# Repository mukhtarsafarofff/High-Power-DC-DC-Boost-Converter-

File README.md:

(ENG)  A boost converter is a DC-DC type switching converter that steps up the voltage while maintaining a constant power balance. This  high-efficiency boost converter circuit based on the popular TL494 IC, which has a minimum supply voltage of 7V and a maximum of 40V.Here i have used IF540N Mosfet as Switch.When the MOSFET is on, the inductor starts charging, the current through the inductor keeps on increasing, which gets stored in the form of a magnetic field.When the  MOSFET turns off, the magnetic field starts to collapse, and the current flows in the direction opposite of the charging current and it starts charging the capacitor.By continuously making the switch (MOSFET) on and off, I have created an output voltage that is greater than the input voltage. Now, i can control the output voltage by controlling the on and the off-time of the switch, and that is what we are doing in the main circuit. The 5V internal reference regulator output of TL494 IC's is the REF pin, which is pin-14 of the IC. The reference regulator is there to provide a stable supply for internal circuitry like the pulse-steering flip-flop, oscillator, dead-time control comparator, and PWM comparator.The frequency of the oscillator can be set by selecting timing components RT and CT. The regulator is also used to drive the error amplifiers which are responsible for controlling the output.The oscillator generates and provides a sawtooth wave to the dead time controller and the PWM comparators for various control signals and the oscillator frequency is equal to the output frequency only for single-ended applications. For push-pull applications, the output frequency is one-half of the oscillator frequency.This IC has two internal output transistors which are in open-collector and open-emitter configurations, by which it can source or sink a maximum current up to 200mA.This circuit can handle a maximum current of 19Amps,so when we want more Amps we need to change our inductor to biggest one .This TL494 Boost Converter circuit is made up of components that are very easily obtainable and this circuit can easily handle power more than 100Watts.If we are connecting a big load to the output of this boost converter circuit, a huge amount of current will flow through the PCB traces, and there's a chance that the traces will burn out. So, to prevent the PCB traces from burning out, we have increased the trace thickness as much as possible. Also, we have reinforced the PCB traces with a thick layer of solder to lower the trace resistance.When we want to  construct this circuit in handmade PCB , we must  reinforce the PCB traces with a thick layer of solder to lower the trace resistance and we need to attach a heatsink to the mosfet.To test the circuit I have used 12V power supply as input.I have attached a voltmeter and an ammeter to the output of the circuit which shows the output voltage and output current. From which we can easily calculate the output power for this circuit. 

(DEU)   Ein Aufwärtswandler ist ein Gleichstrom-Gleichstrom-Schaltwandler, der die Spannung erhöht und gleichzeitig ein konstantes Leistungsgleichgewicht aufrechterhält. Diese hocheffiziente Aufwärtswandlerschaltung basiert auf dem beliebten TL494-IC, der eine minimale Versorgungsspannung von 7 V und eine maximale Versorgungsspannung von 40 V hat. Da wir den IRF540N MOSFET als Schalter verwenden.Während der MOSFET eingeschaltet bleibt, beginnt die Spule sich aufzuladen, der Strom durch die Spule steigt ständig an, was in Form eines Magnetfeldes gespeichert wird.Wenn der MOSFET sich ausschaltet, beginnt das Magnetfeld zusammenzubrechen, und der Strom fließt in die entgegengesetzte Richtung des Ladevorgangsstroms und dies beginnt den Kondesator aufzuladen.Indem ich den Schalter (MOSFET) kontinuierlich ein- und ausschalten, habe ich  eine Ausgangsspannung erzeugt, die größer ist als die Eingangsspannung.Jetzt kann ich die Ausgangsspannung kontrollieren, indem ich die Ein- und Ausschaltzeit des Schalters steuere, und das ist es, was wir im Hauptkreis tun.Die Ausgabe des internen Referenzreglers mit 5V des TL494 ICs ist der REF-Pin, der Pin 14 des ICs. Der Referenzregler dient dazu, eine stabile Versorgung für die interne Schaltung wie den Pulslenk-Flip-Flop, den Oszillator, den Totzeitregelkomparator und den PWM-Komparator bereitzustellen.Die Frequenz des Oszillators kann durch Auswahl der Zeitkomponenten RT und CT eingestellt werden.Der Regler wird auch verwendet, um die Fehlerverstärker anzutreiben, die für die Steuerung des Ausgangs verantwortlich sind.Der Oszillator erzeugt und liefert eine Sägezahnwelle an den Totzeitregler und die PWM-Komparatoren für verschiedene Steuersignale, und die Oszillatorfrequenz entspricht nur für einseitige Anwendungen der Ausgangsfrequenz.Für Gegentaktschaltungen beträgt die Ausgangsfrequenz die Hälfte der Oszillatorfrequenz.Der IC verfügt über zwei interne Ausgangstransistoren, die in Open-Collector- und Open-Emitter-Konfigurationen sind, wodurch er maximal einen Strom von bis zu 200 mA liefern oder aufnehmen kann.Diese Schaltung kann einen maximalen Strom von 19 Ampere handhaben. Wenn wir eine große Last an den Ausgang dieses Boost-Konverter-Schaltkreises anschließen, wird eine enorme Menge an Strom durch die Leiterbahnen der Leiterplatte fließen, und es besteht die Gefahr, dass die Leiterbahnen durchbrennen.Um das Durchbrennen der Leiterbahnen zu verhindern, haben wir die Leiterbahndicke so weit wie möglich erhöht. Außerdem haben wir die Leiterbahnen der Leiterplatte mit einer dicken Schicht Lötzinn verstärkt, um den Leiterbahnwiderstand zu verringern.Wenn wir diesen Schaltkreis auf einer handgefertigten Leiterplatte herstellen möchten, müssen wir die Leiterbahnen der Leiterplatte mit einer dicken Schicht Lötzinn verstärken, um den Leiterbahnwiderstand zu verringern, und wir müssen einen Kühlkörper an den MOSFET anbringen. Wenn wir diesen Schaltkreis auf einer handgefertigten Leiterplatte herstellen möchten, müssen wir die Leiterbahnen der Leiterplatte mit einer dicken Schicht Lötzinn verstärken, um den Leiterbahnwiderstand zu verringern, und wir müssen einen Kühlkörper an den MOSFET anbringen. Um den Schaltkreis zu testen, habe ich eine 12-Volt-Stromversorgung als Eingang verwendet.Ich habe ein Voltmeter und ein Amperemeter an den Ausgang des Schaltkreises angeschlossen, die die Ausgangsspannung und den Ausgangsstrom anzeigen. Dadurch können wir die Ausgangsleistung für diesen Schaltkreis leicht berechnen.

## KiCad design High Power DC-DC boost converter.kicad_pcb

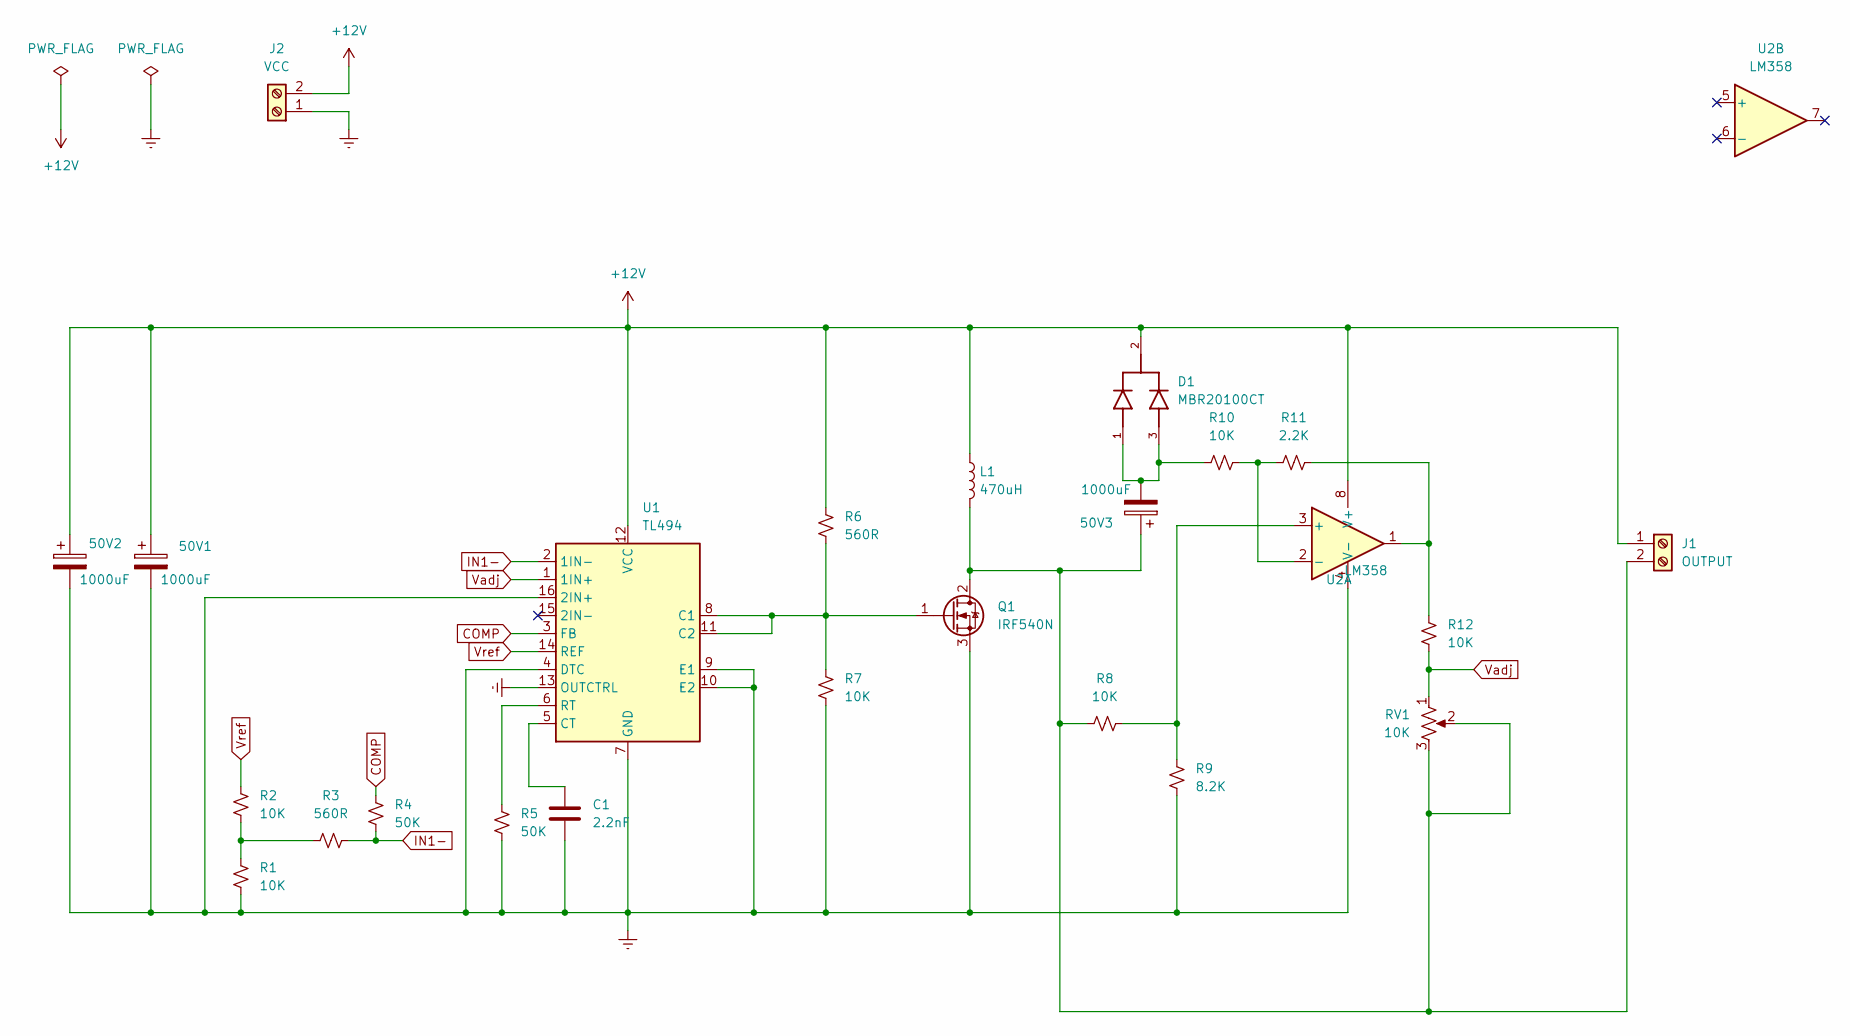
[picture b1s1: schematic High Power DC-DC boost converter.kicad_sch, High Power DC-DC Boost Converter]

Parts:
50V1, 50V2, 50V3: 1000uF; CP_Radial_D13.0mm_P7.50mm
C1: 2.2nF; C_Disc_D7.5mm_W5.0mm_P7.50mm
D1: MBR20100CT; TO254P1066X482X2286-3; PARTREV 8-2
J1: OUTPUT; TerminalBlock_bornier-2_P5.08mm
J2: VCC; TerminalBlock_bornier-2_P5.08mm
L1: 470uH; L_Toroid_Vertical_L24.6mm_W15.5mm_P11.44mm_Pulse_KM-4
Q1: IRF540N; TO-220-3_Vertical
R1, R2, R7, R8, R10, R12: 10K; R_Axial_DIN0411_L9.9mm_D3.6mm_P15.24mm_Horizontal
R3, R6: 560R; R_Axial_DIN0411_L9.9mm_D3.6mm_P15.24mm_Horizontal
R4, R5: 50K; R_Axial_DIN0411_L9.9mm_D3.6mm_P15.24mm_Horizontal
R9: 8.2K; R_Axial_DIN0411_L9.9mm_D3.6mm_P15.24mm_Horizontal
R11: 2.2K; R_Axial_DIN0411_L9.9mm_D3.6mm_P15.24mm_Horizontal
RV1: 10K; Potentiometer_Vishay_148-149_Single_Horizontal
U1: TL494; DIP-16_W7.62mm
U2: LM358; DIP-8_W7.62mm

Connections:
+12V: 50V1.1, 50V2.1, D1.2, J1.1, J2.2, L1.1, R6.2, U1.12 (VCC), U2.8 (V+)
COMP: R4.2, U1.3 (FB)
Earth: 50V1.2, 50V2.2, C1.2, J2.1, Q1.3 (S), R1.2, R5.1, R7.1, R9.2, U1.4 (DTC), U1.7 (GND), U1.9 (E1), U1.10 (E2), U1.13 (OUTCTRL), U1.16 (2IN+), U2.4 (V-)
IN1-: R3.2, R4.1, U1.2 (1IN-)
unnamed: 50V3.2, D1.1, D1.3, R10.2
unnamed: 50V3.1, J1.2, L1.2, Q1.2 (D), R8.2, RV1.2, RV1.3
unnamed: Q1.1 (G), R6.1, R7.2, U1.8 (C1), U1.11 (C2)
unnamed: R1.1, R2.2, R3.1
unnamed: R11.1, R12.1, U2.1
unnamed: C1.1, U1.5 (CT)
unnamed: R5.2, U1.6 (RT)
unnamed: R8.1, R9.1, U2.3 (+)
unnamed: R10.1, R11.2, U2.2 (-)
Vadj: R12.2, RV1.1, U1.1 (1IN+)
Vref: R2.1, U1.14 (REF)

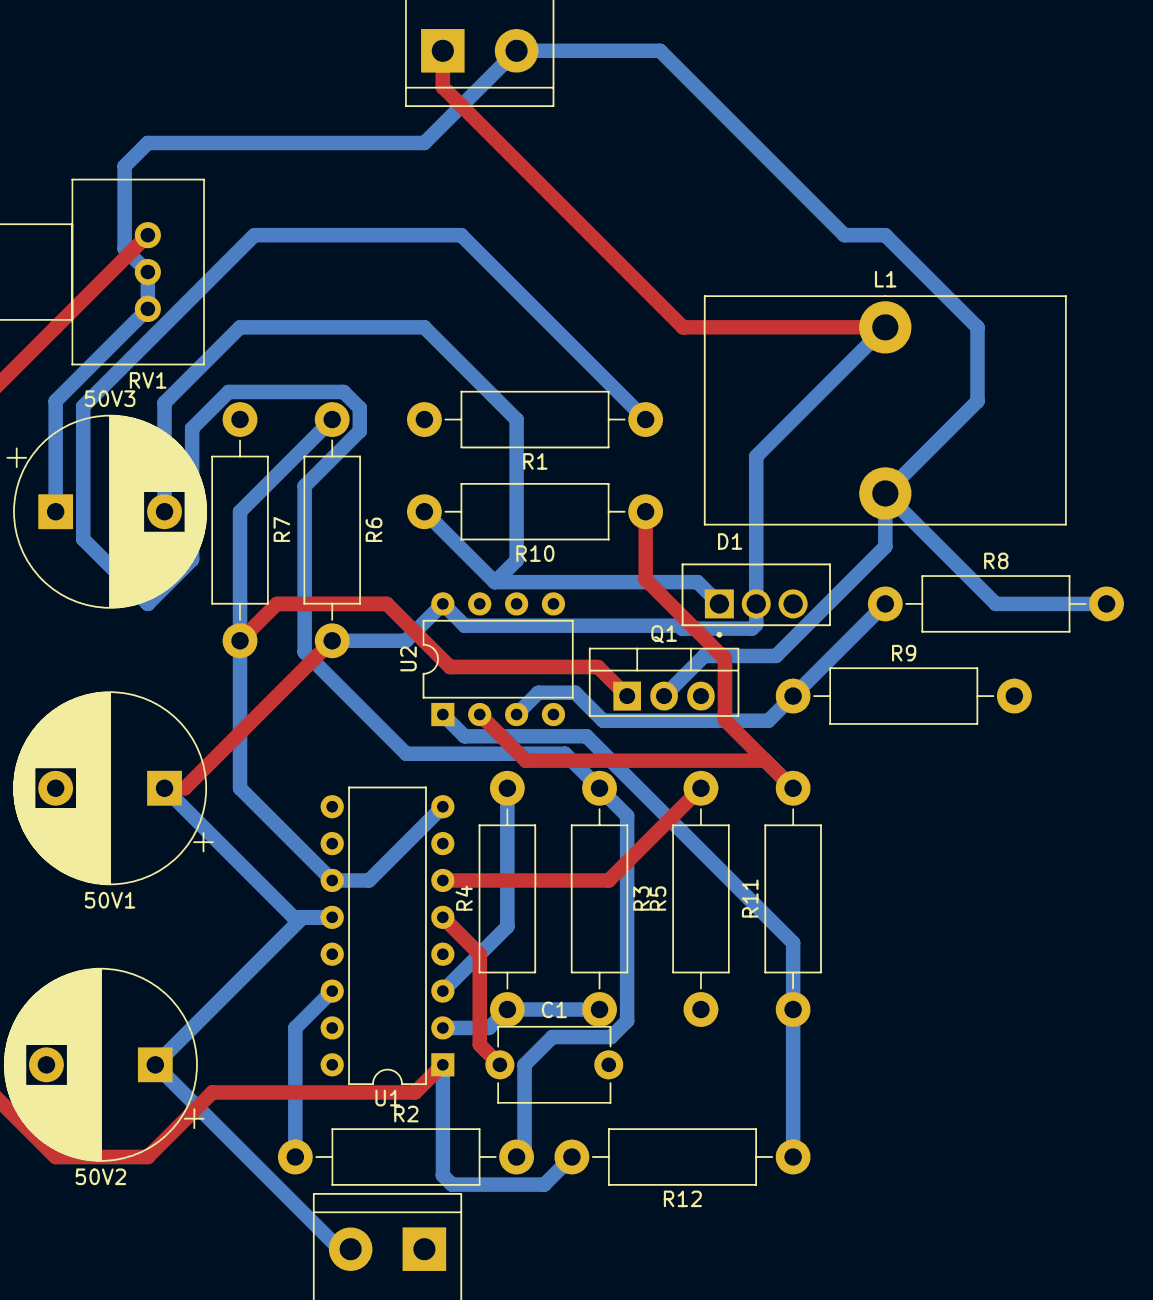
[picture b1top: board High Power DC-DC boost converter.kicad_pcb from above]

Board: 2 copper layers, 24 parts (0 on the bottom side), 15 nets.

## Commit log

2024-03-30 High Power DC-DC Boost Converter is accomplished
